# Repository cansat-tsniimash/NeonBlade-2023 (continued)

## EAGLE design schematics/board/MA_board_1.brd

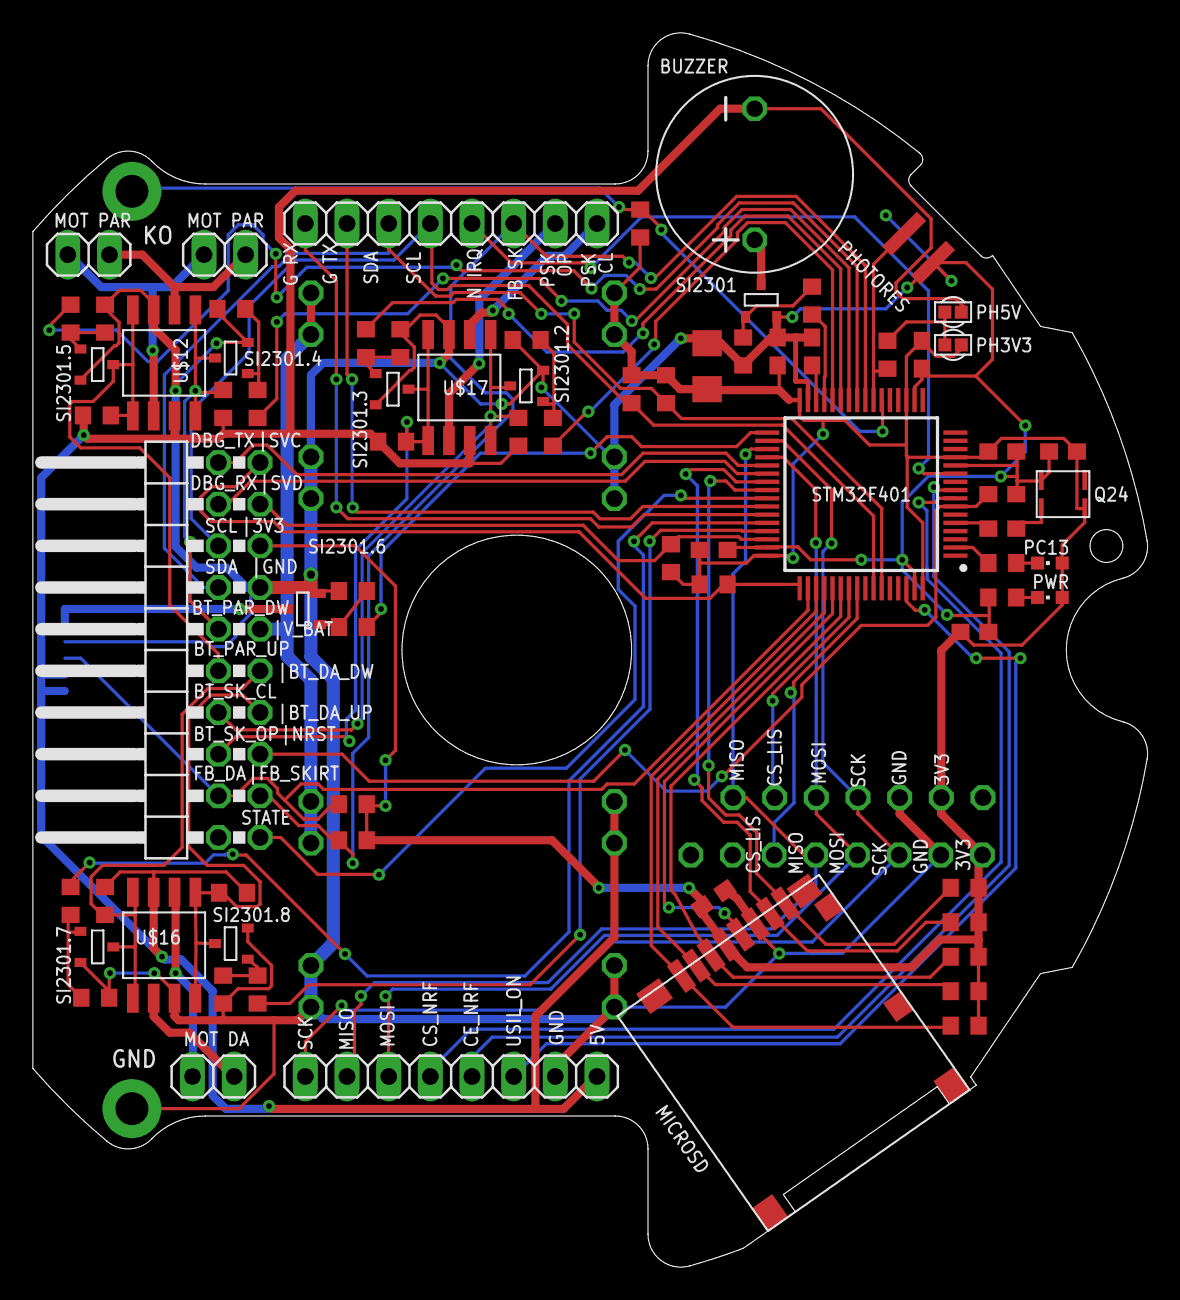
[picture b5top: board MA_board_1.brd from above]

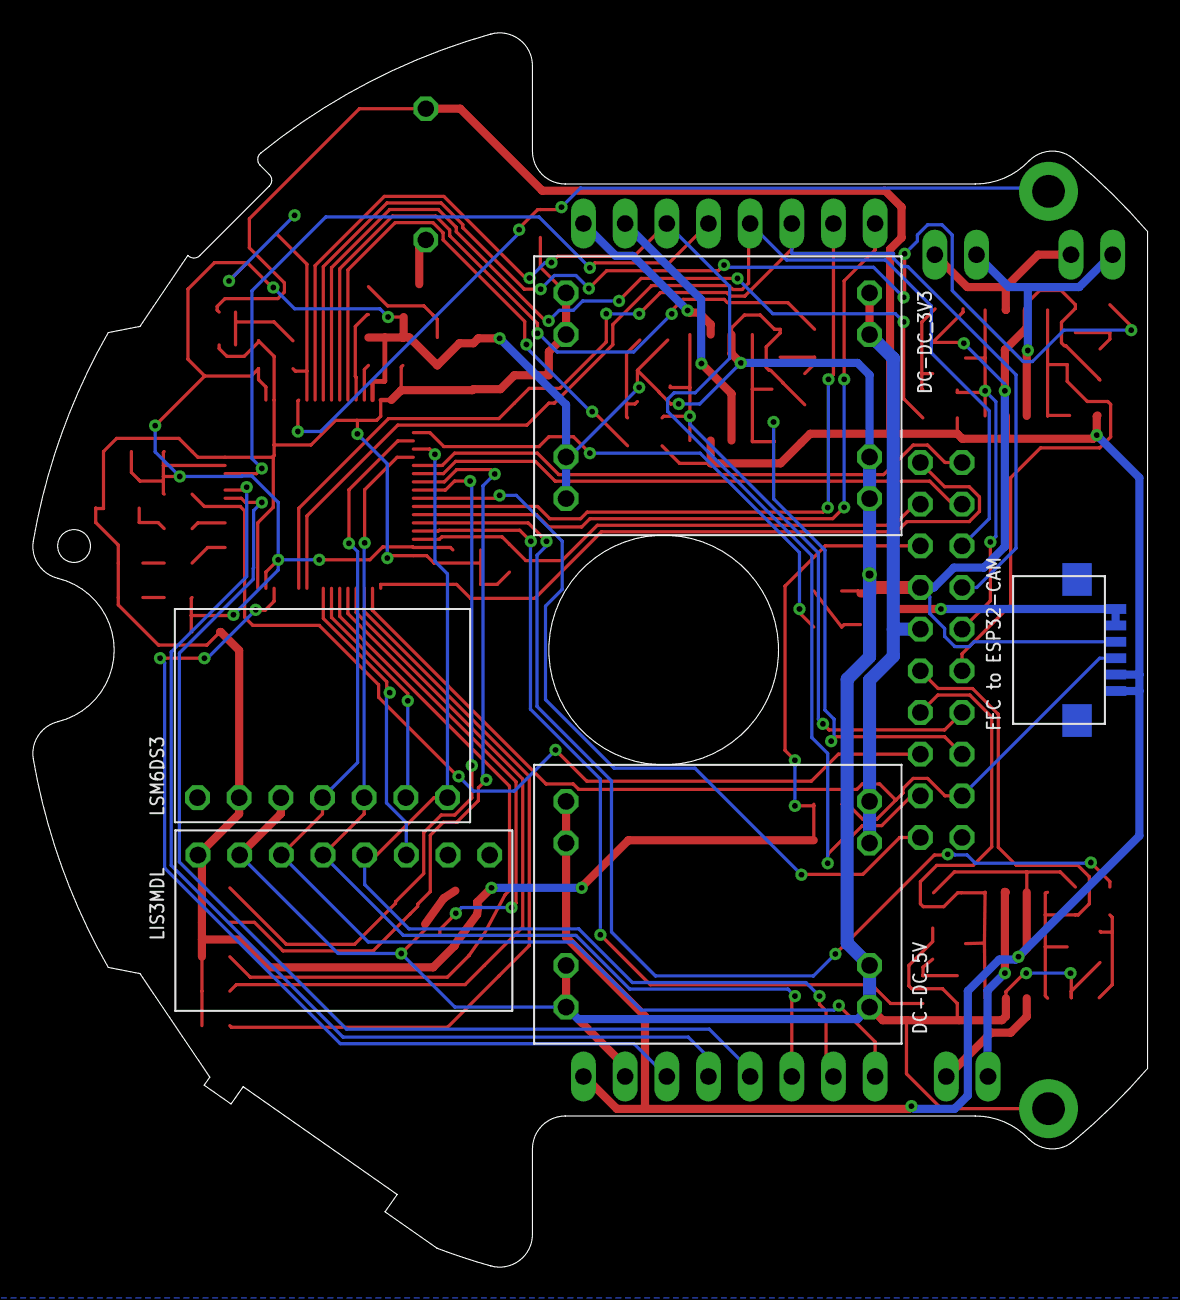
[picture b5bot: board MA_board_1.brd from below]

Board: 2 copper layers, 68.0 x 75.2 mm, 79 parts (3 on the bottom side), 70 nets.

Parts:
3V3, 5V: VIAS-CONNECT
BUZZER: BUZZERS8R6; BUZZER-S8R12
C1, C3, C4, C5, C6, C7, C9: 100nF; C0603
C2: 10uF; C1206
C8: 1nF; C0603
C10: 10nF; C0603
C11: 4.7uf; C0603
DC-DC_3V3, DC-DC_5V: MP1584-B
JP1: 2X10/90
JP2, JP3, JP4: 1X02
JP6, JP7: 1X08
LIS3MDL: LIS3MDL-CJMCUБез_отв._зеркальный; LIS3MDL-CGMSU-NB2023
LSM6DS3: LSM6DS3-GY-NB2023
MICROSD: SD
PC13: CHIPLED_0603
PHOTORES: PHOTORES_VT93N1; PHOTORES_VT93N1_SMD
PWR: CHIPLED_0603
Q24: Q24
R1, R5, R6, R11, R12, R13, R14, R18, R19, R20, R21, R24, R25, R26, R27, R31, R33, R35: 10k; R0603
R2, R7, R8, R9, R10: 3k3; R0603
R3, R4: 2k; R0603
R15, R16, R22, R23, R28, R29, R30, R34: 100R; R0603
R17: 191k/2k; R0603
R32: 3k9; R0603
R36, R37: 4k7; R0603
SI2301, SI2301.2, SI2301.3, SI2301.4, SI2301.5, SI2301.6, SI2301.7, SI2301.8: MOSFET-N; SOT23-3
STM32F401: STM32F401RCT6; QFP50P1200X1200X160-64N
U$8: FCC-CONNECT-6P; FFC-CONNECT-6P-SMD
U$12, U$16, U$17: MOSFET_2P+2N_AP9930GM; SO8

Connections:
3V3: 3V3.1, C1.2, C2.1, C3.2, C4.1, C5.1, C6.1, C7.2, C10.2, DC-DC_3V3.P$7, DC-DC_3V3.P$8, JP1.15, LIS3MDL.P$1, LSM6DS3.P$6, MICROSD.VDD, PC13.A, PWR.A, Q24.P$4, R1.2, R2.2, R5.2, R6.2, R7.2, R8.2, R9.2, R10.2, R32.1, R35.1, R36.2, R37.2, STM32F401.13, STM32F401.19, STM32F401.32, STM32F401.48, STM32F401.64
5V: 5V.2, BUZZER.P$2, DC-DC_5V.P$7, DC-DC_5V.P$8, JP6.8, R12.2, R13.2, R19.2, R20.2, R25.2, R26.2, U$8.P$5, U$8.P$6, U$12.7, U$16.7, U$17.7
BASS_BUZZER: R30.1, STM32F401.29
BOTTON_DA_DOWN: JP1.9, R13.1, SI2301.7.3, U$16.1, U$16.8
BOTTON_DA_UP: JP1.7, R12.1, SI2301.8.3, U$16.4, U$16.5
BOTTON_PAR_DOWN: JP1.12, R20.1, SI2301.4.3, U$12.1, U$12.8
BOTTON_PAR_UP: JP1.10, R19.1, SI2301.5.3, U$12.4, U$12.5
BOTTON_SKIRT_CLOSE: JP1.8, R26.1, SI2301.2.3, U$17.1, U$17.8
BOTTON_SKIRT_OPEN: JP1.6, R25.1, SI2301.3.3, U$17.4, U$17.5
CE_NRF: JP6.5, STM32F401.9
CS_LIS: LIS3MDL.P$6, STM32F401.56
CS_LSM: LSM6DS3.P$2, STM32F401.55
CS_NRF: JP6.4, STM32F401.8
DBG_RX: JP1.18, STM32F401.38
DBG_TX: JP1.20, STM32F401.37
ESP_EN: R34.1, STM32F401.33
FEEDBACK_DA: JP1.4, R35.2, STM32F401.50, U$8.P$4
FEEDBACK_SKIRT: JP1.3, JP7.6, R1.1, STM32F401.24
GND: C1.1, C2.2, C3.1, C4.2, C5.2, C6.2, C7.1, C9.1, C10.1, C11.2, DC-DC_3V3.P$3, DC-DC_3V3.P$4, DC-DC_3V3.P$5, DC-DC_3V3.P$6, DC-DC_5V.P$3, DC-DC_5V.P$4, DC-DC_5V.P$5, DC-DC_5V.P$6, JP1.13, JP6.7, LIS3MDL.P$2, LSM6DS3.P$5, MICROSD.VSS, PHOTORES.P$1, Q24.P$2, R3.1, R11.1, R14.1, R18.1, R21.1, R24.1, R27.1, R31.2, R33.1, SI2301.2, SI2301.2.2, SI2301.3.2, SI2301.4.2, SI2301.5.2, SI2301.6.2, SI2301.7.2, SI2301.8.2, STM32F401.12, STM32F401.18, STM32F401.31, STM32F401.47, STM32F401.63, U$8.P$3, U$12.3, U$16.3, U$17.3
GND_ESP: SI2301.6.3, U$8.P$1, U$8.P$2
GPS_RX: JP7.1, STM32F401.43
GPS_TX: JP7.2, STM32F401.42
KO: R32.2, STM32F401.22
LED: R4.1, STM32F401.2
MISO: JP6.2, LIS3MDL.P$5, LSM6DS3.P$1, STM32F401.35
MOSI: JP6.3, LIS3MDL.P$4, LSM6DS3.P$3, STM32F401.36
MOTOR_DA_DOWN: R15.1, STM32F401.44
MOTOR_DA_UP: R16.2, STM32F401.45
MOTOR_PAR_DOWN: R22.1, STM32F401.26
MOTOR_PAR_UP: R23.2, STM32F401.25
MOTOR_SKIRT_CLOSE: R28.1, STM32F401.28
MOTOR_SKIRT_OPEN: R29.2, STM32F401.27
unnamed: R30.2, R31.1, SI2301.1
unnamed: R11.2, R15.2, SI2301.7.1
unnamed: R18.2, R22.2, SI2301.4.1
unnamed: R33.2, R34.2, SI2301.6.1
unnamed: JP3.1, JP4.1, U$12.2
unnamed: JP2.1, U$16.2
unnamed: JP2.2, U$16.6
unnamed: R14.2, R16.1, SI2301.8.1
unnamed: JP3.2, JP4.2, U$12.6
unnamed: C8.2, Q24.P$3
unnamed: R21.2, R23.1, SI2301.5.1
unnamed: C11.1, STM32F401.30
unnamed: 3V3.2, 5V.1, R17.1
unnamed: R24.2, R28.2, SI2301.2.1
unnamed: R27.2, R29.1, SI2301.3.1
unnamed: BUZZER.P$1, SI2301.3
unnamed: PWR.C, R3.2
unnamed: PC13.C, R4.2
NRF_IRQ: JP7.5, STM32F401.11
NRST: C9.2, JP1.5, STM32F401.7
PHOTORES: PHOTORES.P$2, R17.2, STM32F401.23
POWER_SKIRT_CLOSE: JP7.8, U$17.2
POWER_SKIRT_OPEN: JP7.7, U$17.6
SCK: JP6.1, LIS3MDL.P$3, LSM6DS3.P$4, STM32F401.34
SCL: JP1.16, JP7.4, R37.1, STM32F401.58
SDA: JP1.14, JP7.3, R36.1, STM32F401.59
SDIO_CK: MICROSD.CLK, STM32F401.53
SDIO_CMD: MICROSD.CMD, R8.1, STM32F401.54
SDIO_DAT0: MICROSD.DAT0, R9.1, STM32F401.39
SDIO_DAT1: MICROSD.DAT1, R10.1, STM32F401.40
SDIO_DAT2: MICROSD.DAT2, R2.1, STM32F401.51
SDIO_DAT3: MICROSD.DAT3, R7.1, STM32F401.52
STATE: JP1.1, STM32F401.41
SVC: JP1.19, R6.1, STM32F401.49
SVD: JP1.17, R5.1, STM32F401.46
TCXO: C8.1, STM32F401.5
USIL_ON: JP6.6, STM32F401.62
V_BAT: DC-DC_3V3.P$1, DC-DC_3V3.P$2, DC-DC_5V.P$1, DC-DC_5V.P$2, JP1.11

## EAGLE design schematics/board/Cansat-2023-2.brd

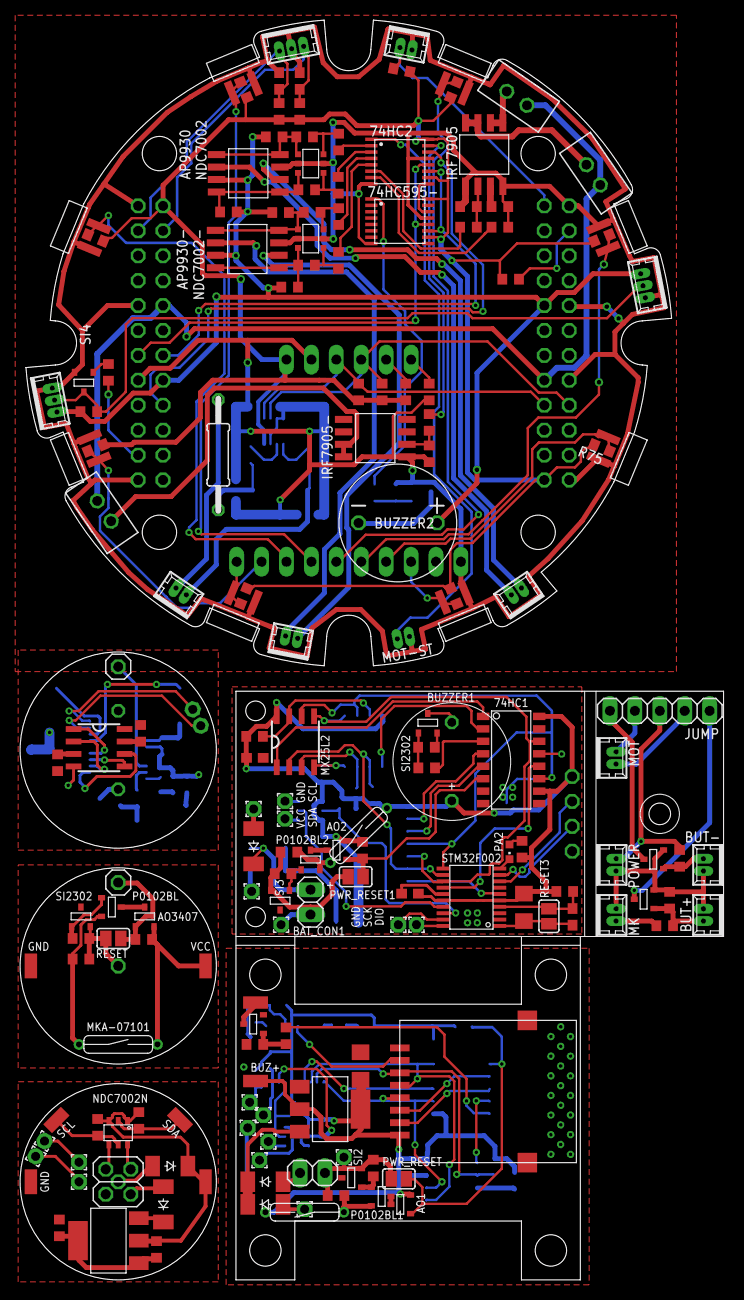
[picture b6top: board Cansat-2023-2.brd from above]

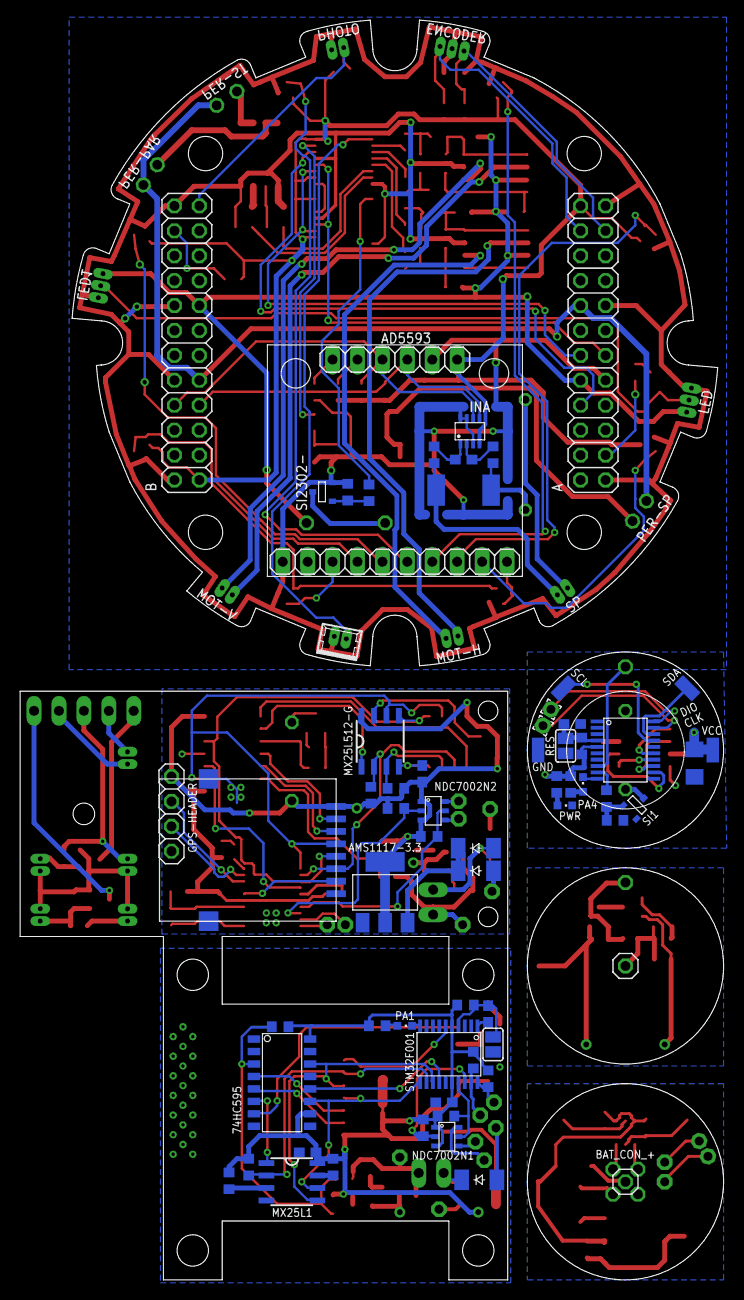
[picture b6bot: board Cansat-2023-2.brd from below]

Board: 2 copper layers, 71.7 x 128.4 mm, 233 parts (65 on the bottom side), 178 nets.

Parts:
74HC1, 74HC595: 74HC595SOIC16; SOIC16
74HC2, 74HC595-: 74HC595; TSSOP16
A: 2X12
AD5593: AD5593
AMS1117, AMS1117-3.3, AMS1117-ADJ: AMS1117; SOT223
AO1, AO2, AO3407: AO3407A; SOT23-3
AP9930, AP9930-: AP9930GM; SO8
B: 2X12
BAT_CON, BAT_CON1: 1X02
BAT_CON_-: 1X01
BUT+: 53047-02
BUT-: 53047-02
BUZ, BUZ1: SI2302CDS; SOT23-3
BUZ+: SMD1,27-2,54
BUZ-: SMD1,27-2,54
BUZZER, BUZZER1: BUZZER-5V; BUZZER
BUZZER2: BUZZERS8R6; BUZZER-S8R12
C1, C3, C8: 10µF; C1206
C2, C4, C5, C6, C7, C9, C10, C11, C12, C13, C14: 100nF; C0603
CHRG, CHRG1: 1,6/0,9
E01-ML01SP1, E01-ML01SP4: E01-ML01SP4
ENCODER: MOLEX-3-1.25; 53047-03
GND, GND1, GND2: SMD1,27-2,54
GND3, GND4: 1,6/0,9
GPS-HEADER: 1X04
INA: INA219AID; SOT23-8
IRF7905, IRF7905-: IRF7905; SO8
JP1: 2X02
JP2, JP3: 1X01
JUMP: 1X05
LED, LED1: MOLEX-3-1.25; 53047-03
MK: 53047-02
MOT: 53047-02
MOT-H: MOLEX-2-1.25; 53047-02
MOT-ST: MOLEX-2-1.25; 53047-02
MOT-V: MOLEX-2-1.25; 53047-02
MX25L1, MX25L2, MX25L512, MX25L512-G: MX25L25645; SOP8
NDC7002, NDC7002-: NDC7002N; SOT23-6
NDC7002N, NDC7002N1, NDC7002N2: NDC7002N; SOT-23-6
P0102BL, P0102BL1, P0102BL2: P0102BL; SOT23-3
PA1, PA2, PA4: CHIPLED_0603
PAD1, PAD2: 1,6/0,9
PER-PAR: JST-2-2.5
PER-SP: JST-2-2.5
PER-ST: JST-2-2.5
PHOTO: MOLEX-2-1.25; 53047-02
POWER: 53047-02
PWR: CHIPLED_0603
PWR-CTRL: 1X01
PWR_RESET, PWR_RESET1: SJ
R1, R8, R14, R16, R18, R30, R32, R43: 1k; R0603
R2: 1k4; R0603
R3, R4, R84: 4k7; R0603
R5: 10k x2; R0603
R6, R7, R35, R36, R37, R41, R44, R50, R52, R53, R54, R55, R59, R66, R67, R68, R70, R85: 10k; R0603
R9, R11, R12, R13, R15, R17, R19, R20, R21, R22, R23, R24, R25, R26, R27, R28, R29, R31, R33, R34, R38, R39, R40, R58, R61, R62, R63, R80, R81: 5k1; R0603
R10: 1k*2; R0603
R42: 10k*2; R0603
R45, R51, R56, R57, R60, R64, R65, R69, R83: 100R; R0603
R46, R47: 10R; R0603
R48: R01; R2512
R49: 10k*3; R0603
R71: 100R; 0207/15
R72, R73, R74, R75, R76, R77, R78, R79, R82: 2k; R0603
RESET, RESET1, RESET2, RESET3: SJ
SCL, SCL1: SMD1,27-2,54
SCL2, SCL3: 1,6/0,9
SDA, SDA1: SMD1,27-2,54
SDA2, SDA3: 1,6/0,9
SI1, SI2, SI3, SI4, SI2302, SI2302-: SI2302CDS; SOT23-3
SP: MOLEX-2-1.25; 53047-02
STM32F001, STM32F002, STM32F042: STM32F042F6P6; TSSOP-20
SW: 1,6/0,9
SWC, SWC1, SWC2: 1,6/0,9
SWD, SWD1, SWD2, SWD3: 1,6/0,9
U$1, U$2, U$4, U$5, U$6, U$8, U$9, U$10: MBR0530T1G; SOD-123_MINI-SMA
U$3, U$7: МКА-07101
U$11, U$21: SI2302CDS; SOT23-3
U$12, U$15, U$17, U$18, U$19, U$22, U$23, U$24: VT93N1
VCC, VCC1, VCC2: SMD1,27-2,54
VIN, VIN1: 1,6/0,9
МКА-07101: МКА-07101

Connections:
3V3: 74HC2.10, 74HC2.16, 74HC595-.10, 74HC595-.16, A.24, AD5593.16, B.1, INA.4, R61.2, R62.1, R63.1, R72.2, R73.2, R74.2, R75.2, R76.2, R77.2, R78.2, R79.2, R80.2, R81.2, R82.2, R85.2
5V: A.10, AP9930.7, AP9930-.7, B.15, BUZZER2.P$2, LED.1, LED1.1, R49.2, R50.2, R66.2, R67.2, R84.1
12V: JUMP.3, POWER.2, R41.2
BUZZER: R18.2, STM32F042.9
BUZZER1: 74HC595.7, R14.2
BUZZER2: 74HC1.3, R30.2
BUZZER3: 74HC595-.1, R45.1
CS: MX25L512.1, STM32F042.15
ENCOD_A: A.21, C14.2, ENCODER.1, R80.1
ENCOD_B: A.22, C13.2, ENCODER.3, R81.1
FOTO1: AD5593.3, R73.1, U$17.P$2
FOTO2: AD5593.4, R75.1, U$12.P$1
FOTO3: AD5593.5, R72.1, U$18.P$2
FOTO4: AD5593.6, R76.1, U$19.P$1
FOTO5: AD5593.7, R77.1, U$22.P$1
FOTO6: AD5593.8, R79.1, U$24.P$2
FOTO7: AD5593.9, R78.1, U$23.P$1
FOTO8: AD5593.10, R74.1, U$15.P$2
FOTO9: B.23, PHOTO.1, R82.1
GND: GND.1, JP1.2, R2.2
GND1: GND1.1, SI2302.3
GND2: C3.1, C4.1, GND2.1, MX25L512.4, PWR.C, R17.2, RESET1.1, SI1.2, STM32F042.1, STM32F042.16
GND3: 74HC595.8, 74HC595.13, AMS1117.P$2, BUZ.2, C1.1, C2.1, C5.1, C6.1, E01-ML01SP4.8, E01-ML01SP4.9, E01-ML01SP4.10, MX25L1.4, R13.2, RESET2.1, SI2.3, STM32F001.1, STM32F001.15
GND4: PA1.C, STM32F001.10
GND5: 74HC1.8, 74HC1.13, AMS1117-3.3.1, BUZ1.2, C7.1, C8.1, C9.1, C10.1, C11.1, E01-ML01SP1.8, E01-ML01SP1.9, E01-ML01SP1.10, GPS-HEADER.4, MX25L2.4, MX25L512-G.4, R29.2, RESET3.1, SI3.3, STM32F002.1, STM32F002.15
GND6: PA2.C, STM32F002.10
GND7: BUT+.1, BUT-.2, MK.2, POWER.1, R42.2, U$11.2, U$21.2
GND8: 74HC2.8, 74HC2.13, 74HC595-.8, 74HC595-.13, A.1, A.9, A.15, A.23, AD5593.1, AD5593.15, AP9930.3, AP9930-.3, B.2, B.10, B.16, B.24, C13.1, C14.1, ENCODER.2, INA.3, INA.7, INA.8, IRF7905.1, IRF7905.4, IRF7905-.1, LED.3, LED1.3, MOT-ST.2, NDC7002.2, NDC7002.5, NDC7002-.2, NDC7002-.5, PHOTO.2, R54.2, R55.2, R57.1, R58.2, R59.2, R70.2, SI4.2, SI2302-.2, U$12.P$2, U$15.P$1, U$17.P$1, U$18.P$1, U$19.P$2, U$22.P$2, U$23.P$2, U$24.P$1
HLD: MX25L2.7, MX25L512-G.7, R39.1
INA_SP+: R47.1, R48.2, R71.1
IRQ: E01-ML01SP4.7, STM32F001.6
IRQ1: E01-ML01SP1.7, STM32F002.6
LATCH: 74HC595.12, STM32F001.14
LATCH1: 74HC1.12, STM32F002.14
LATCH2: 74HC2.12, 74HC595-.12, A.11
LED: A.3, R83.1
MEM_CS: 74HC595.6, MX25L1.1
MEM_CS1: 74HC1.1, MX25L2.1
MEM_G_CS: 74HC1.2, MX25L512-G.1
MISO: MX25L512.2, STM32F042.13
MISO1: E01-ML01SP4.6, MX25L1.2, R26.1, STM32F001.12
MISO2: E01-ML01SP1.6, MX25L2.2, MX25L512-G.2, R38.1, STM32F002.12
MK_MOTOR1+: 74HC2.4, R69.2
MK_MOTOR1-: 74HC2.5, R51.2
MK_MOTOR2+: 74HC2.2, R64.2
MK_MOTOR2-: 74HC2.3, R65.2
MOSI: MX25L512.5, STM32F042.14
MOSI1: 74HC595.14, E01-ML01SP4.5, MX25L1.5, STM32F001.13
MOSI2: 74HC1.14, E01-ML01SP1.5, MX25L2.5, MX25L512-G.5, STM32F002.13
MOSI3: 74HC2.14, A.8
MOTOR1+: AP9930-.6, MOT-H.2
MOTOR1-: AP9930-.2, MOT-H.1
MOTOR2+: AP9930.6, MOT-V.2
MOTOR2-: AP9930.2, MOT-V.1
MOTOR3+: JUMP.4, MOT.2
MOTOR3+G: JUMP.5, U$21.3
MOTOR3-: JUMP.2, MOT.1
MOTOR3-G: JUMP.1, U$11.3
unnamed: JP1.1, U$1.A
unnamed: JP2.1, U$2.A
unnamed: AMS1117-ADJ.P$1, AMS1117-ADJ.P$2, R1.2, R2.1
unnamed: NDC7002N.5, R3.1, SCL.1
unnamed: PAD2.1, SWD.1
unnamed: NDC7002N.2, R4.1, SDA.1
unnamed: P0102BL.1, R5.1, SI2302.1
unnamed: P0102BL.2, R6.1, МКА-07101.1
unnamed: AO3407.3, P0102BL.3
unnamed: BAT_CON_-.1, R5.2, R6.2, RESET.2, SI2302.2
unnamed: AO3407.1, PWR-CTRL.1, R7.1, RESET.1
unnamed: PWR.A, R10.2
unnamed: R17.1, R18.1, SI1.1
unnamed: BUZZER.-, SI1.3
unnamed: PA4.A, R8.2
unnamed: PA4.C, STM32F042.10
unnamed: JP3.1, STM32F042.8
unnamed: MX25L512.3, R11.1
unnamed: MX25L512.7, R12.1
unnamed: STM32F042.20, SWC.1
unnamed: STM32F042.19, SWD1.1
unnamed: BUZ.1, R13.1, R14.1
unnamed: BUZ.3, BUZ-.1
unnamed: R27.1, STM32F001.20, SWC1.1
unnamed: PA1.A, R16.2
unnamed: P0102BL1.1, R21.1, SI2.1
unnamed: P0102BL1.2, R22.1, U$3.1
unnamed: AO1.3, P0102BL1.3
unnamed: BAT_CON.2, GND3.1, PWR_RESET.2, R21.2, R22.2, SI2.2
unnamed: MX25L1.7, R24.1
unnamed: MX25L1.3, R25.2
unnamed: BAT_CON.1, U$4.A, U$5.C
unnamed: U$6.A, VIN.1
unnamed: CHRG.1, U$5.A
unnamed: R28.1, STM32F001.19, SWD2.1
unnamed: NDC7002N1.6, SCL2.1
unnamed: BUZ1.1, R29.1, R30.1
unnamed: BUZ1.3, BUZZER1.-
unnamed: PA2.A, R32.2
unnamed: P0102BL2.1, R35.1, SI3.1
unnamed: P0102BL2.2, R36.1, U$7.1
unnamed: AO2.3, P0102BL2.3
unnamed: BAT_CON1.2, GND4.1, PWR_RESET1.2, R35.2, R36.2, SI3.2
unnamed: U$8.A, VIN1.1
unnamed: CHRG1.1, U$9.A
unnamed: BAT_CON1.1, U$9.C, U$10.A
unnamed: STM32F002.20, SWC2.1
unnamed: STM32F002.19, SWD3.1
unnamed: BUT-.1, R41.1, U$21.1
unnamed: BUT+.2, R42.1, R43.2, U$11.1
unnamed: BUZZER2.P$1, SI2302-.3
unnamed: R45.2, R70.1, SI2302-.1
unnamed: C12.1, INA.1, R46.2
unnamed: C12.2, INA.2, R47.2
unnamed: AP9930.1, AP9930.8, NDC7002.6, R49.1, R53.1
unnamed: NDC7002.3, R44.2, R64.1
unnamed: NDC7002.1, R53.2, R65.1
unnamed: AP9930.4, AP9930.5, NDC7002.4, R44.1, R50.1
unnamed: AP9930-.1, AP9930-.8, NDC7002-.6, R52.1, R66.1
unnamed: NDC7002-.3, R68.2, R69.1
unnamed: NDC7002-.1, R51.1, R52.2
unnamed: AP9930-.4, AP9930-.5, NDC7002-.4, R67.1, R68.1
unnamed: IRF7905.3, R54.1
unnamed: IRF7905.2, R55.1, R56.1
unnamed: IRF7905-.2, R59.1, R60.1
unnamed: AD5593.12, R61.1
unnamed: AD5593.11, R58.1
unnamed: R83.2, SI4.1
unnamed: LED.2, LED1.2, R84.2, SI4.3
unnamed: 74HC2.9, 74HC595-.14
PERE1: 74HC2.6, R56.2
PERE1_G: IRF7905.7, IRF7905.8, PER-PAR.1
PERE2: 74HC2.7, R57.2
PERE2_G: IRF7905.5, IRF7905.6, PER-ST.1
PERE3: 74HC2.15, R60.2
PERE3_G: IRF7905-.7, IRF7905-.8, PER-SP.1
PWR_CTRL: 74HC595.3, AO1.1, PWR_RESET.1, R23.1
PWR_CTRL1: 74HC1.6, AO2.1, PWR_RESET1.1, R37.1
RESET: C4.2, R9.2, RESET1.2, STM32F042.4
RESET1: C5.2, R15.2, RESET2.2, STM32F001.4
RESET2: C9.2, R31.2, RESET3.2, STM32F002.4
RF-CS: 74HC595.4, E01-ML01SP4.3
RF_CE: 74HC595.5, E01-ML01SP4.2
RF_CE1: 74HC1.4, E01-ML01SP1.2
RF_CS: 74HC1.5, E01-ML01SP1.3
RX: GPS-HEADER.3, STM32F002.9
SCK: MX25L512.6, STM32F042.12
SCK1: 74HC595.11, E01-ML01SP4.4, MX25L1.6, STM32F001.11
SCK2: 74HC1.11, E01-ML01SP1.4, MX25L2.6, MX25L512-G.6, STM32F002.11
SCK3: 74HC2.11, 74HC595-.11, A.12
SCL: JP1.3, NDC7002N.6
SCL1: SCL1.1, STM32F042.17
SCL2: AD5593.14, B.7, INA.5, R63.2
SCL-A: NDC7002N2.6, SCL3.1
SCL-B: NDC7002N1.5, R19.1, STM32F001.17
SCL-B1: NDC7002N2.5, R33.1, STM32F002.17
SDA: JP1.4, NDC7002N.4
SDA1: SDA1.1, STM32F042.18
SDA2: AD5593.13, B.8, INA.6, R62.2
SDA-A: NDC7002N1.4, SDA2.1
SDA-A1: NDC7002N2.4, SDA3.1
SDA-B: NDC7002N1.2, R20.1, STM32F001.18
SDA-B1: NDC7002N2.2, R34.1, STM32F002.18
SP+: R46.1, R48.1, SP.1
SP-: R71.2, SP.2
SWC: PAD1.1, SW.1
SWITCH: B.22, R85.1
TRUBKI: MK.1, R43.1
TRUBKI1: 74HC2.1, MOT-ST.1
TX: GPS-HEADER.2, STM32F002.8
VAB: A.16, B.9, PER-PAR.2, PER-SP.2, PER-ST.2
VCC: AMS1117-ADJ.P$3, NDC7002N.1, NDC7002N.3, R1.1, R3.2, R4.2, U$2.C, VCC.1
VCC1: AO3407.2, R7.2, VCC1.1, МКА-07101.2
VCC2: BUZZER.+, C3.2, MX25L512.8, R8.1, R9.1, R10.1, R11.2, R12.2, STM32F042.5, VCC2.1
VCC3: 74HC595.10, 74HC595.16, AMS1117.P$1, AMS1117.P$3, AO1.2, BUZ+.1, C1.2, C2.2, C6.2, E01-ML01SP4.1, MX25L1.8, NDC7002N1.1, NDC7002N1.3, R15.1, R16.1, R19.2, R20.2, R23.2, R24.2, R25.1, R26.2, R27.2, R28.2, STM32F001.5, STM32F001.16, U$3.2
VCC4: 74HC1.10, 74HC1.16, AMS1117-3.3.2, AMS1117-3.3.4, AO2.2, BUZZER1.+, C7.2, C8.2, C10.2, C11.2, E01-ML01SP1.1, GPS-HEADER.1, MX25L2.8, MX25L512-G.8, NDC7002N2.1, NDC7002N2.3, R31.1, R32.1, R33.2, R34.2, R37.2, R38.2, R39.2, R40.2, STM32F002.5, STM32F002.16, U$7.2
VCC/1: AMS1117.P$4, U$4.C, U$6.C
VCC/2: AMS1117-ADJ.P$4, U$1.C
VCC/3: AMS1117-3.3.3, U$8.C, U$10.C
WP: MX25L2.3, MX25L512-G.3, R40.1

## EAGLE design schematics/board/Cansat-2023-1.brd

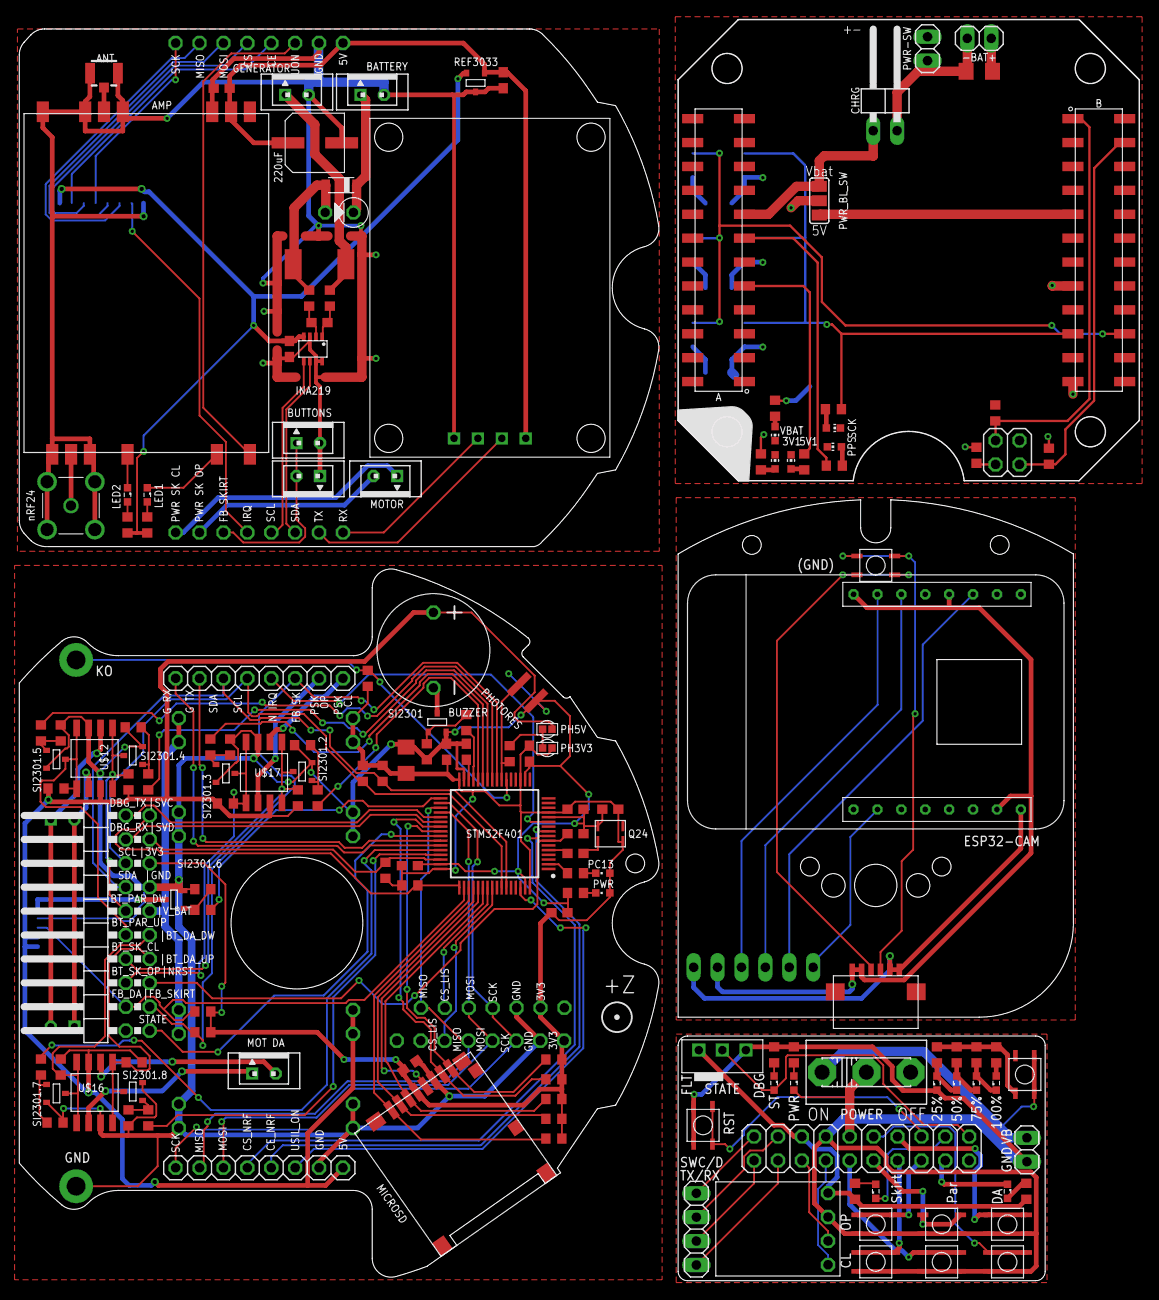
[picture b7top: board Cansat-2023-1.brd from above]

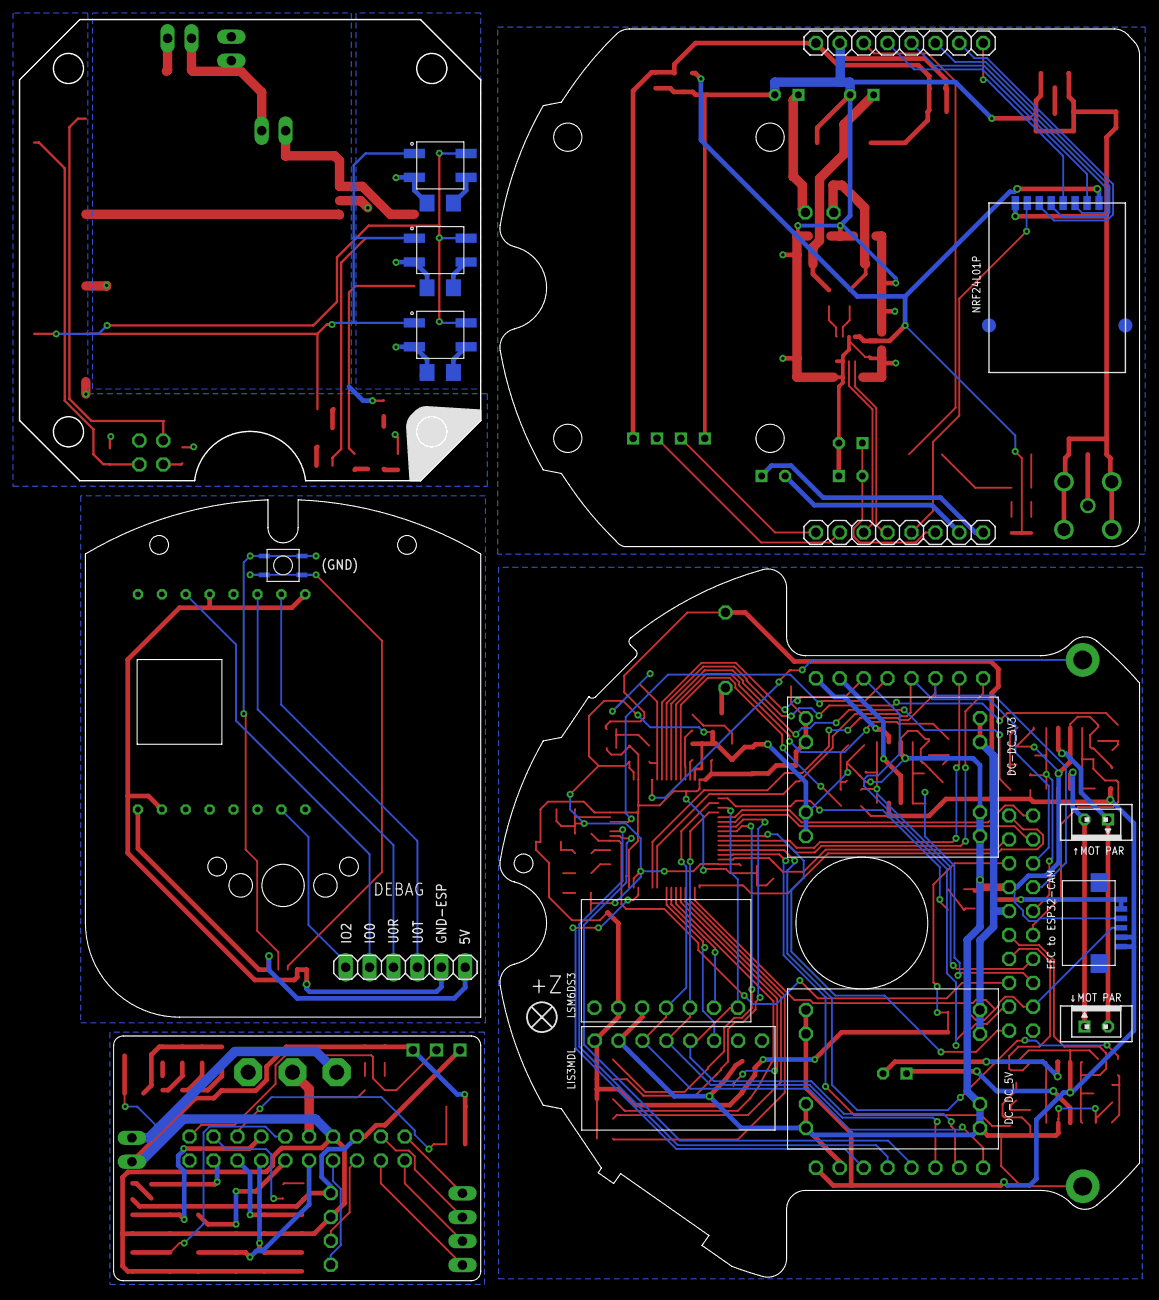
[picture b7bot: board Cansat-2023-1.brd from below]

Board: 2 copper layers, 119.0 x 134.0 mm, 169 parts (16 on the bottom side), 152 nets.

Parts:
1, 2, 3: 4-PIN; 4PINHEADERSMD
3V1, 5V1: CHIP-LED0603
3V3, 5V: VIAS-CONNECT
-BAT+: 1X02
A: 24-PIN; 24PINHEADERSMD
AMP: XQ-02A
B: 24-PIN; 24PINHEADERSMD
BATTERY: JST-2-K-S; B2B-PH-K-S
BUTTON-OP: JST-2-K-S; B2B-PH-K-S
BUTTONS: JST-2-K-S; B2B-PH-K-S
BUZZER: BUZZERS8R6; BUZZER-S8R12
C1, C3, C4, C5, C6, C7, C9, C12, C13, C14, C15: 100nF; C0603
C2: 10uF; C1206
C8: 1nF; C0603
C10: 10nF; C0603
C11: 4.7uf; C0603
C16: 220uF; ECAP220-CMD
C17, C18, C19, C20: 10µF; C1206
CHRG: 1X02/90
D1: D-MBR; SOD123
DC-DC_3V3, DC-DC_5V: MP1584-B
DEBAG: 1X06
DIP-4A: BA159
ESP32-CAM: ESP32-CAM
GENERATOR: JST-2-K-S; B2B-PH-K-S
INA219: INA219AID; SOT23-8
J1: MCX-J-P-H-ST-TH1; MCXJPHSTTH1
J2: U.FL-R-SMT-1_10_; U.FL-R-SMT-1(10)
JP1: 2X10/90
JP2, JP3, JP4: JST-2-K-S; B2B-PH-K-S
JP5: 1X04
JP6, JP7, JP11, JP12: 1X08
JP8: 1X02
JP9: 2X10
JP10: 2X02
LED1, LED2, LED3, LED4, LED5, LED6, LED7, LED8, LED9, LED10: SML0603
LIS3MDL: LIS3MDL-CJMCUБез_отв._зеркальный; LIS3MDL-CGMSU-NB2023
LSM6DS3: LSM6DS3-GY-NB2023
MICROSD: SD
MOTOR: JST-2-K-S; B2B-PH-K-S
NRF24L01P: NRF24L01_ML01SP4
PC13: CHIPLED_0603
PHOTORES: PHOTORES_VT93N1; PHOTORES_VT93N1_SMD
PPS: CHIP-LED0603
PWR: CHIPLED_0603
PWR-SW: 1X02
PWR_BL_SW: SJ_2
Q24: Q24
R1, R5, R6, R11, R12, R13, R14, R18, R19, R20, R21, R24, R25, R26, R27, R31, R33, R35: 10k; R0603
R2, R7, R8, R9, R10: 3k3; R0603
R3, R4, R40, R41, R47, R48, R50, R52, R54: 2k; R0603
R15, R16, R22, R23, R28, R29, R30, R34, R38, R39, R57: 100R; R0603
R17: 191k/2k; R0603
R32: 3k9; R0603
R36, R37: 4k7; R0603
R42: R05; R2512
R43, R44, R45, R46, R51, R53, R58: 1k; R0603
R49: 5K1; R0603
R55: R0603
R56: 5k1; R0603
REF3033: REF3033; SOT23-3
S1: UNICS-SWITCH
SCK: CHIP-LED0603
SI2301, SI2301.2, SI2301.3, SI2301.4, SI2301.5, SI2301.6, SI2301.7, SI2301.8: MOSFET-N; SOT23-3
STM32F401: STM32F401RCT6; QFP50P1200X1200X160-64N
U$1, U$8: FCC-CONNECT-6P; FFC-CONNECT-6P-SMD
U$2, U$3, U$6, U$7, U$9, U$10, U$11, U$13, U$14, U$15: BTN_VERY_SMALL
U$4: BME280BME280-PINS-ONLY; BME280-PINS-ONLY
U$5: GPS
U$12, U$16, U$17: MOSFET_2P+2N_AP9930GM; SO8
U$18: MSS12D01
VBAT: CHIP-LED0603

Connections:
3V1: C14.2, INA219.4, NRF24L01P.P$1, R40.2, R41.2, REF3033.2
3V2: JP9.15, R47.2, R48.2, U$4.P$1, U$18.P$2
3V3: 3V3.1, C1.2, C2.1, C3.2, C4.1, C5.1, C6.1, C7.2, C10.2, DC-DC_3V3.P$7, DC-DC_3V3.P$8, JP1.15, LIS3MDL.P$1, LSM6DS3.P$6, MICROSD.VDD, PC13.A, PWR.A, Q24.P$4, R1.2, R2.2, R5.2, R6.2, R7.2, R8.2, R9.2, R10.2, R32.1, R35.1, R36.2, R37.2, STM32F401.13, STM32F401.19, STM32F401.32, STM32F401.48, STM32F401.64
5V: 5V.2, BUZZER.P$1, DC-DC_5V.P$7, DC-DC_5V.P$8, JP6.8, R12.2, R13.2, R19.2, R20.2, R25.2, R26.2, U$8.P$5, U$8.P$6, U$12.7, U$16.7, U$17.7
5V1: AMP.P$5, C12.1, C15.2, C16.P$1, JP11.8, REF3033.1, U$5.UCC
5V2: DEBAG.1, ESP32-CAM.P$1, U$1.P$5, U$1.P$6
+3V3: A.23, B.23, R53.2, R55.2, R57.2
+5V: A.9, B.9, PWR_BL_SW.1, R52.2
BASS_BUZZER: R30.1, STM32F401.29
BOTTON_DA_DOWN: JP1.9, R13.1, SI2301.7.3, U$16.1, U$16.8
BOTTON_DA_DOWN1: JP9.9, U$9.P$1, U$9.P$2
BOTTON_DA_UP: JP1.7, R12.1, SI2301.8.3, U$16.4, U$16.5
BOTTON_DA_UP1: JP9.7, U$10.P$1, U$10.P$2
BOTTON_PAR_DOWN: JP1.12, R20.1, SI2301.4.3, U$12.1, U$12.8
BOTTON_PAR_DOWN1: JP9.12, U$11.P$1, U$11.P$2
BOTTON_PAR_UP: JP1.10, R19.1, SI2301.5.3, U$12.4, U$12.5
BOTTON_PAR_UP1: JP9.10, U$13.P$1, U$13.P$2
BOTTON_SKIRT_CLOSE: JP1.8, R26.1, SI2301.2.3, U$17.1, U$17.8
BOTTON_SKIRT_CLOSE1: JP9.8, U$15.P$1, U$15.P$2
BOTTON_SKIRT_OPEN: JP1.6, R25.1, SI2301.3.3, U$17.4, U$17.5
BOTTON_SKIRT_OPEN1: JP9.6, U$14.P$1, U$14.P$2
CE_NRF: JP6.5, STM32F401.9
CE_NRF1: JP11.5, NRF24L01P.P$2
CS_LIS: LIS3MDL.P$6, STM32F401.56
CS_LSM: LSM6DS3.P$2, STM32F401.55
CS_NRF: JP6.4, STM32F401.8
CS_NRF1: JP11.4, NRF24L01P.P$3
DBG_RX: JP1.18, STM32F401.38
DBG_RX1: JP5.1, JP9.18
DBG_TX: JP1.20, STM32F401.37
DBG_TX1: JP5.2, JP9.20
ESP_EN: R34.1, STM32F401.33
FEEDBACK_DA: JP1.4, R35.2, STM32F401.50, U$8.P$4
FEEDBACK_DA1: U$1.P$4, U$2.P$1, U$2.P$2, U$3.P$1, U$3.P$2
FEEDBACK_DA2: JP9.4, LED8.C
FEEDBACK_SKIRT: JP1.3, JP7.6, R1.1, STM32F401.24
FEEDBACK_SKIRT1: BUTTON-OP.2, BUTTONS.1, JP12.6
FEEDBACK_SKIRT2: JP9.3, LED7.C
GND: C1.1, C2.2, C3.1, C4.2, C5.2, C6.2, C7.1, C9.1, C10.1, C11.2, DC-DC_3V3.P$3, DC-DC_3V3.P$4, DC-DC_3V3.P$5, DC-DC_3V3.P$6, DC-DC_5V.P$3, DC-DC_5V.P$4, DC-DC_5V.P$5, DC-DC_5V.P$6, JP1.13, JP6.7, LIS3MDL.P$2, LSM6DS3.P$5, MICROSD.VSS, PHOTORES.P$1, Q24.P$2, R3.1, R11.1, R14.1, R18.1, R21.1, R24.1, R27.1, R31.2, R33.1, SI2301.2, SI2301.2.2, SI2301.3.2, SI2301.4.2, SI2301.5.2, SI2301.6.2, SI2301.7.2, SI2301.8.2, STM32F401.12, STM32F401.18, STM32F401.31, STM32F401.47, STM32F401.63, U$8.P$3, U$12.3, U$16.3, U$17.3
GND1: AMP.P$1, AMP.P$2, AMP.P$4, AMP.P$10, AMP.P$12, AMP.P$13, BATTERY.2, BUTTON-OP.1, BUTTONS.2, C12.2, C14.1, C15.1, C16.P$2, GENERATOR.2, INA219.3, INA219.7, INA219.8, J1.2, J1.3, J1.4, J1.5, J2.1, J2.2, JP11.7, NRF24L01P.P$8, REF3033.3, U$5.GND
GND2: U$1.P$3, U$2.P$3, U$2.P$4, U$3.P$3, U$3.P$4
GND3: JP8.2, JP9.13, LED3.C, R49.2, R50.2, U$4.P$2, U$7.P$3, U$7.P$4, U$9.P$3, U$9.P$4, U$10.P$3, U$10.P$4, U$11.P$3, U$11.P$4, U$13.P$3, U$13.P$4, U$14.P$3, U$14.P$4, U$15.P$3, U$15.P$4, U$18.P$3
GND4: 1.3, 2.3, 3.3, 3V1.C, 5V1.C, A.2, A.10, A.16, A.24, B.2, B.10, B.16, B.24, C18.1, C19.1, C20.1, JP10.1, PPS.C, PWR-SW.1, R56.1, SCK.C, VBAT.C
GND_ESP: SI2301.6.3, U$8.P$1, U$8.P$2
GND_ESP1: DEBAG.2, ESP32-CAM.P$2, ESP32-CAM.P$12, ESP32-CAM.P$16, U$1.P$1, U$1.P$2
GPS_RX: JP7.1, STM32F401.43
GPS_RX1: JP12.1, U$5.TX
GPS_TX: JP7.2, STM32F401.42
GPS_TX1: JP12.2, U$5.RX
IO0: DEBAG.5, ESP32-CAM.P$11
IO2: DEBAG.6, ESP32-CAM.P$7
KO: R32.2, STM32F401.22
LED: R4.1, STM32F401.2
LED1: AMP.P$8, LED1.C
LED2: AMP.P$9, LED2.C
MISO: JP6.2, LIS3MDL.P$5, LSM6DS3.P$1, STM32F401.35
MISO1: JP11.2, NRF24L01P.P$6
MOSI: JP6.3, LIS3MDL.P$4, LSM6DS3.P$3, STM32F401.36
MOSI1: JP11.3, NRF24L01P.P$5
MOTOR_DA_DOWN: R15.1, STM32F401.44
MOTOR_DA_UP: R16.2, STM32F401.45
MOTOR_PAR_DOWN: R22.1, STM32F401.26
MOTOR_PAR_UP: R23.2, STM32F401.25
MOTOR_SKIRT_CLOSE: R28.1, STM32F401.28
MOTOR_SKIRT_OPEN: R29.2, STM32F401.27
unnamed: R30.2, R31.1, SI2301.1
unnamed: R11.2, R15.2, SI2301.7.1
unnamed: R18.2, R22.2, SI2301.4.1
unnamed: R33.2, R34.2, SI2301.6.1
unnamed: JP3.1, JP4.2, U$12.2
unnamed: JP2.1, U$16.2
unnamed: JP2.2, U$16.6
unnamed: R14.2, R16.1, SI2301.8.1
unnamed: JP3.2, JP4.1, U$12.6
unnamed: C8.2, Q24.P$3
unnamed: R21.2, R23.1, SI2301.5.1
unnamed: C11.1, STM32F401.30
unnamed: 3V3.2, 5V.1, R17.1
unnamed: R24.2, R28.2, SI2301.2.1
unnamed: C13.1, INA219.1, R38.2
unnamed: C13.2, INA219.2, R39.2
unnamed: R27.2, R29.1, SI2301.3.1
unnamed: BATTERY.1, D1.C, DIP-4A.P$2
unnamed: GENERATOR.1, R38.1, R42.1
unnamed: BUZZER.P$2, SI2301.3
unnamed: AMP.P$3, J2.3
unnamed: AMP.P$11, J1.1
unnamed: LED1.A, R40.1
unnamed: LED2.A, R41.1
unnamed: D1.A, DIP-4A.P$1, R39.1, R42.2
unnamed: LED3.A, LED4.C, R43.2
unnamed: LED4.A, LED5.C, R44.2
unnamed: LED5.A, LED6.C, R45.2
unnamed: LED6.A, R46.2
unnamed: JP8.1, S1.1, U$6.P$1, U$6.P$2
unnamed: LED7.A, R47.1
unnamed: LED8.A, R48.1
unnamed: LED9.C, R49.1
unnamed: LED10.C, R50.1
unnamed: R43.1, R44.1, R45.1, R46.1, U$6.P$3
unnamed: PWR.C, R3.2
unnamed: PC13.C, R4.2
unnamed: R51.1, SCK.A
unnamed: 5V1.A, R52.1
unnamed: 3V1.A, R53.1
unnamed: PPS.A, R54.1
unnamed: -BAT+.2, C17.1, CHRG.2, PWR-SW.2
unnamed: JP10.4, R57.1
unnamed: R58.1, VBAT.A
NRF_IRQ: JP7.5, STM32F401.11
NRF_IRQ1: JP12.5, NRF24L01P.P$7
NRST: C9.2, JP1.5, STM32F401.7
NRST1: JP9.5, U$7.P$1, U$7.P$2
PHOT: B.4, JP10.2, R55.1
PHOTORES: PHOTORES.P$2, R17.2, STM32F401.23
POWER_SKIRT_CLOSE: JP7.8, U$17.2
POWER_SKIRT_CLOSE1: JP12.8, MOTOR.1
POWER_SKIRT_OPEN: JP7.7, U$17.6
POWER_SKIRT_OPEN1: JP12.7, MOTOR.2
PPS: A.13, R54.2
SCK: JP6.1, LIS3MDL.P$3, LSM6DS3.P$4, STM32F401.34
SCK1: JP11.1, NRF24L01P.P$4
SCL: JP1.16, JP7.4, R37.1, STM32F401.58
SCL1: INA219.5, JP12.4
SCL2: JP9.16, U$4.P$3
SCL3: 1.1, 2.1, 3.1, B.19, R51.2
SDA: JP1.14, JP7.3, R36.1, STM32F401.59
SDA1: INA219.6, JP12.3
SDA2: JP9.14, U$4.P$4
SDA3: 1.2, 2.2, 3.2, B.20
SDIO_CK: MICROSD.CLK, STM32F401.53
SDIO_CMD: MICROSD.CMD, R8.1, STM32F401.54
SDIO_DAT0: MICROSD.DAT0, R9.1, STM32F401.39
SDIO_DAT1: MICROSD.DAT1, R10.1, STM32F401.40
SDIO_DAT2: MICROSD.DAT2, R2.1, STM32F401.51
SDIO_DAT3: MICROSD.DAT3, R7.1, STM32F401.52
ST-SW: B.1, JP10.3, R56.2
STATE: JP1.1, STM32F401.41
STATE1: JP9.1, LED10.A, U$18.P$1
SVC: JP1.19, R6.1, STM32F401.49
SVD: JP1.17, R5.1, STM32F401.46
SWC: JP5.4, JP9.19
SWD: JP5.3, JP9.17
TCXO: C8.1, STM32F401.5
U0R: DEBAG.4, ESP32-CAM.P$14
U0T: DEBAG.3, ESP32-CAM.P$15
USIL_ON: JP6.6, STM32F401.62
USIL_ON1: AMP.P$7, JP11.6
V+: -BAT+.1, A.15, B.15, C17.2, CHRG.1, PWR_BL_SW.3, R58.2
VCC: 1.4, 2.4, 3.4, C18.2, C19.2, C20.2, PWR_BL_SW.2
V_BAT: DC-DC_3V3.P$1, DC-DC_3V3.P$2, DC-DC_5V.P$1, DC-DC_5V.P$2, JP1.11
V_BAT1: JP9.11, LED9.A, S1.2

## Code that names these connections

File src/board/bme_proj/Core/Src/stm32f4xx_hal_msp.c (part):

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
    __HAL_RCC_GPIOB_CLK_ENABLE();
    /**I2C1 GPIO Configuration
    PB6     ------> I2C1_SCL
    PB7     ------> I2C1_SDA
    */
    GPIO_InitStruct.Pin = GPIO_PIN_6|I2C1_SDA_Pin;
    GPIO_InitStruct.Mode = GPIO_MODE_AF_OD;
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    __HAL_RCC_I2C1_CLK_DISABLE();

    /**I2C1 GPIO Configuration
    PB6     ------> I2C1_SCL
    PB7     ------> I2C1_SDA
    */
    HAL_GPIO_DeInit(GPIOB, GPIO_PIN_6);

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
    __HAL_RCC_GPIOB_CLK_ENABLE();
    /**SPI2 GPIO Configuration
    PB10     ------> SPI2_SCK
    PB14     ------> SPI2_MISO
    PB15     ------> SPI2_MOSI
    */
    GPIO_InitStruct.Pin = GPIO_PIN_10|GPIO_PIN_14|GPIO_PIN_15;
    GPIO_InitStruct.Mode = GPIO_MODE_AF_PP;
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    __HAL_RCC_SPI2_CLK_DISABLE();

    /**SPI2 GPIO Configuration
    PB10     ------> SPI2_SCK
    PB14     ------> SPI2_MISO
    PB15     ------> SPI2_MOSI
    */
    HAL_GPIO_DeInit(GPIOB, GPIO_PIN_10|GPIO_PIN_14|GPIO_PIN_15);

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
    __HAL_RCC_GPIOA_CLK_ENABLE();
    /**USART1 GPIO Configuration
    PA9     ------> USART1_TX
    PA10     ------> USART1_RX
    */
    GPIO_InitStruct.Pin = GPIO_PIN_9|GPIO_PIN_10;
    GPIO_InitStruct.Mode = GPIO_MODE_AF_PP;
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    __HAL_RCC_USART1_CLK_DISABLE();

    /**USART1 GPIO Configuration
    PA9     ------> USART1_TX
    PA10     ------> USART1_RX
    */
    HAL_GPIO_DeInit(GPIOA, GPIO_PIN_9|GPIO_PIN_10);

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
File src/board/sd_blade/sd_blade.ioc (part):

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Mcu.Name=STM32F411C(C-E)Ux
Mcu.Package=UFQFPN48
Mcu.UserName=STM32F411CEUx
PA6.Mode=SD_1_bit
PA6.Signal=SDIO_CMD
PB15.Mode=SD_1_bit
PB15.Signal=SDIO_CK
PB4.Mode=SD_1_bit
PB4.Signal=SDIO_D0
RCC.HSE_VALUE=25000000
RCC.SYSCLKFreq_VALUE=16000000
board=custom
